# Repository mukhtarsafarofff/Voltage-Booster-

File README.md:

(ENG) This boost converter is used to "step-up" an input voltage to some higher level, required by a load and is based on NE555 and TL431 Integrated Circuits.

(DEU) Dieser Aufwärtswandler wird verwendet, um eine Eingangsspannung auf ein höheres Niveau zu „erhöhen“, das von einer Last benötigt wird, und basiert auf den integrierten Schaltkreisen NE555 und TL431.

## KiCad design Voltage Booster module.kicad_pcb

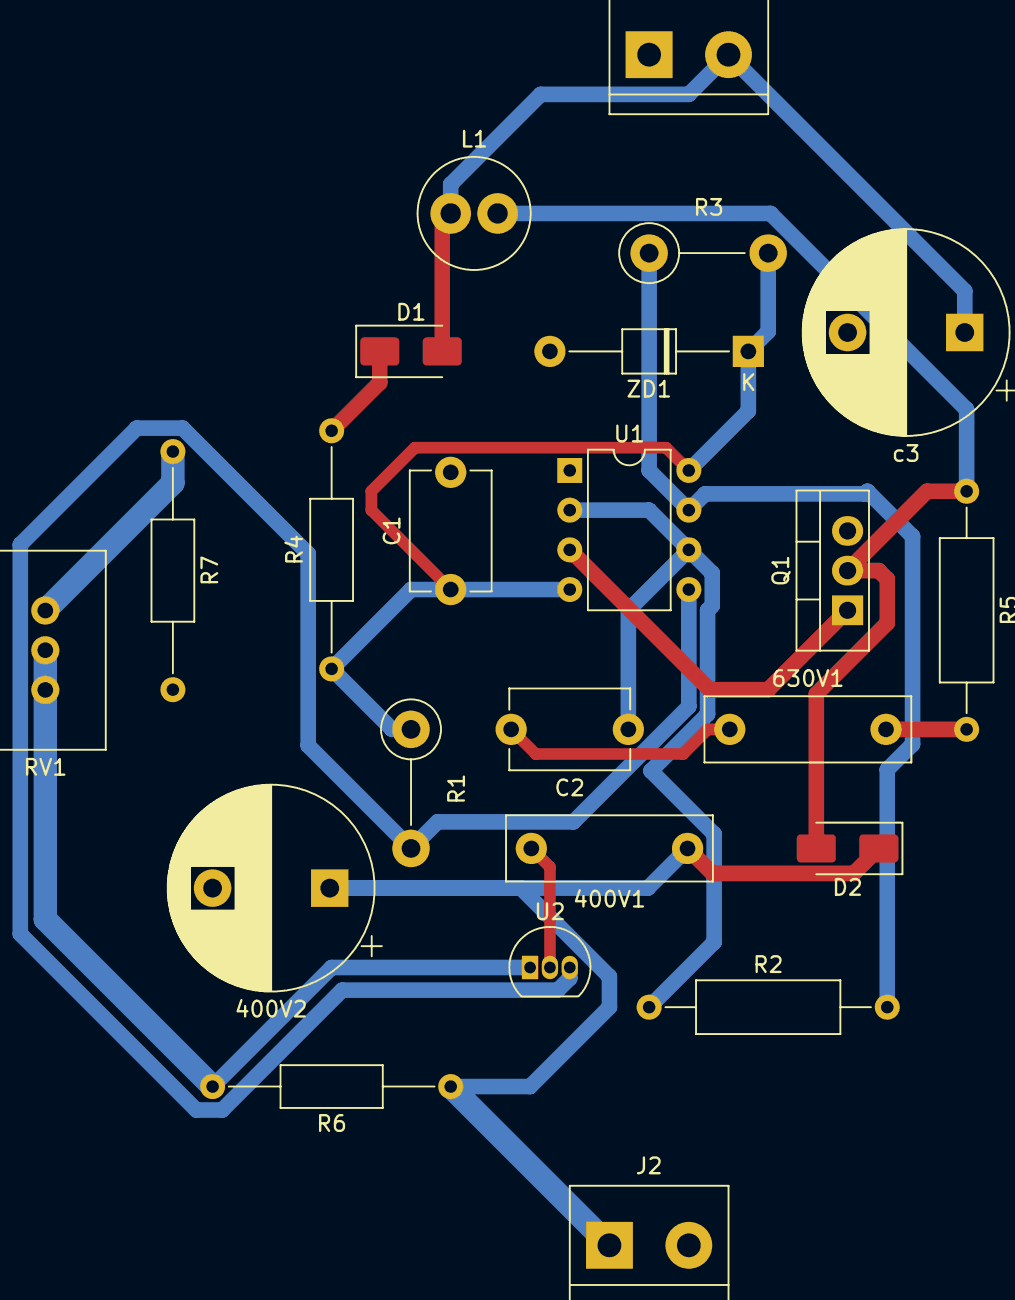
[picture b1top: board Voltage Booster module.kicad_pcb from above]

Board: 2 copper layers, 23 parts (0 on the bottom side), 13 nets.

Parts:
400V1: 10nF; C_Rect_L13.0mm_W4.0mm_P10.00mm_FKS3_FKP3_MKS4
400V2: 22uF; CP_Radial_D13.0mm_P7.50mm
630V1: 100pF; C_Rect_L13.0mm_W4.0mm_P10.00mm_FKS3_FKP3_MKS4
C1: 22uF; C_Disc_D7.5mm_W5.0mm_P7.50mm
C2: 10nF; C_Disc_D7.5mm_W5.0mm_P7.50mm
D1, D2: US1A; D_SMA
J1: INPUT; TerminalBlock_bornier-2_P5.08mm
J2: OUTPUT; TerminalBlock_bornier-2_P5.08mm
L1: 150uH; L_Radial_D7.0mm_P3.00mm
Q1: IRF740; TO-220-3_Vertical
R1, R3: 1K; R_Axial_DIN0411_L9.9mm_D3.6mm_P7.62mm_Vertical
R2: 10K; R_Axial_DIN0309_L9.0mm_D3.2mm_P15.24mm_Horizontal
R4: 330R; R_Axial_DIN0207_L6.3mm_D2.5mm_P15.24mm_Horizontal
R5: 4,7K; R_Axial_DIN0309_L9.0mm_D3.2mm_P15.24mm_Horizontal
R6: 470K; R_Axial_DIN0207_L6.3mm_D2.5mm_P15.24mm_Horizontal
R7: 3,3K; R_Axial_DIN0207_L6.3mm_D2.5mm_P15.24mm_Horizontal
RV1: 10K; Potentiometer_Vishay_148-149_Single_Horizontal
U1: NE555P; DIP-8_W7.62mm
U2: TL431LP; TO-92_Inline
ZD1: 12V; D_T-1_P12.70mm_Horizontal
c3: 1000uF; CP_Radial_D13.0mm_P7.50mm

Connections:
+12V: D1.2 (A), J1.2, L1.1, c3.1
DIS: R2.2, R3.1, U1.7 (DIS)
DIV: C2.1, R2.1, U1.2 (TR), U1.6 (THR)
Earth: 400V1.2, 400V2.2, 630V1.1, C1.2, C2.2, J1.1, J2.2, Q1.3 (S), R7.2, U1.1 (GND), U2.2 (A), ZD1.2 (A), c3.2
unnamed: 630V1.2, R5.2
unnamed: D1.1 (K), R4.2
unnamed: D2.2 (A), L1.2, Q1.2 (D), R5.1
unnamed: 400V1.1, 400V2.1, D2.1 (K), J2.1, R6.1
unnamed: Q1.1 (G), U1.3 (Q)
unnamed: R7.1, RV1.1
unnamed: R1.2, U1.5 (CV), U2.3 (K)
unnamed: R6.2, RV1.2, RV1.3, U2.1 (REF)
Reset: C1.1, R1.1, R3.2, R4.1, U1.4 (R), U1.8 (VCC), ZD1.1 (K)

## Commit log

2024-03-19 Voltage Booster module is accomplished
